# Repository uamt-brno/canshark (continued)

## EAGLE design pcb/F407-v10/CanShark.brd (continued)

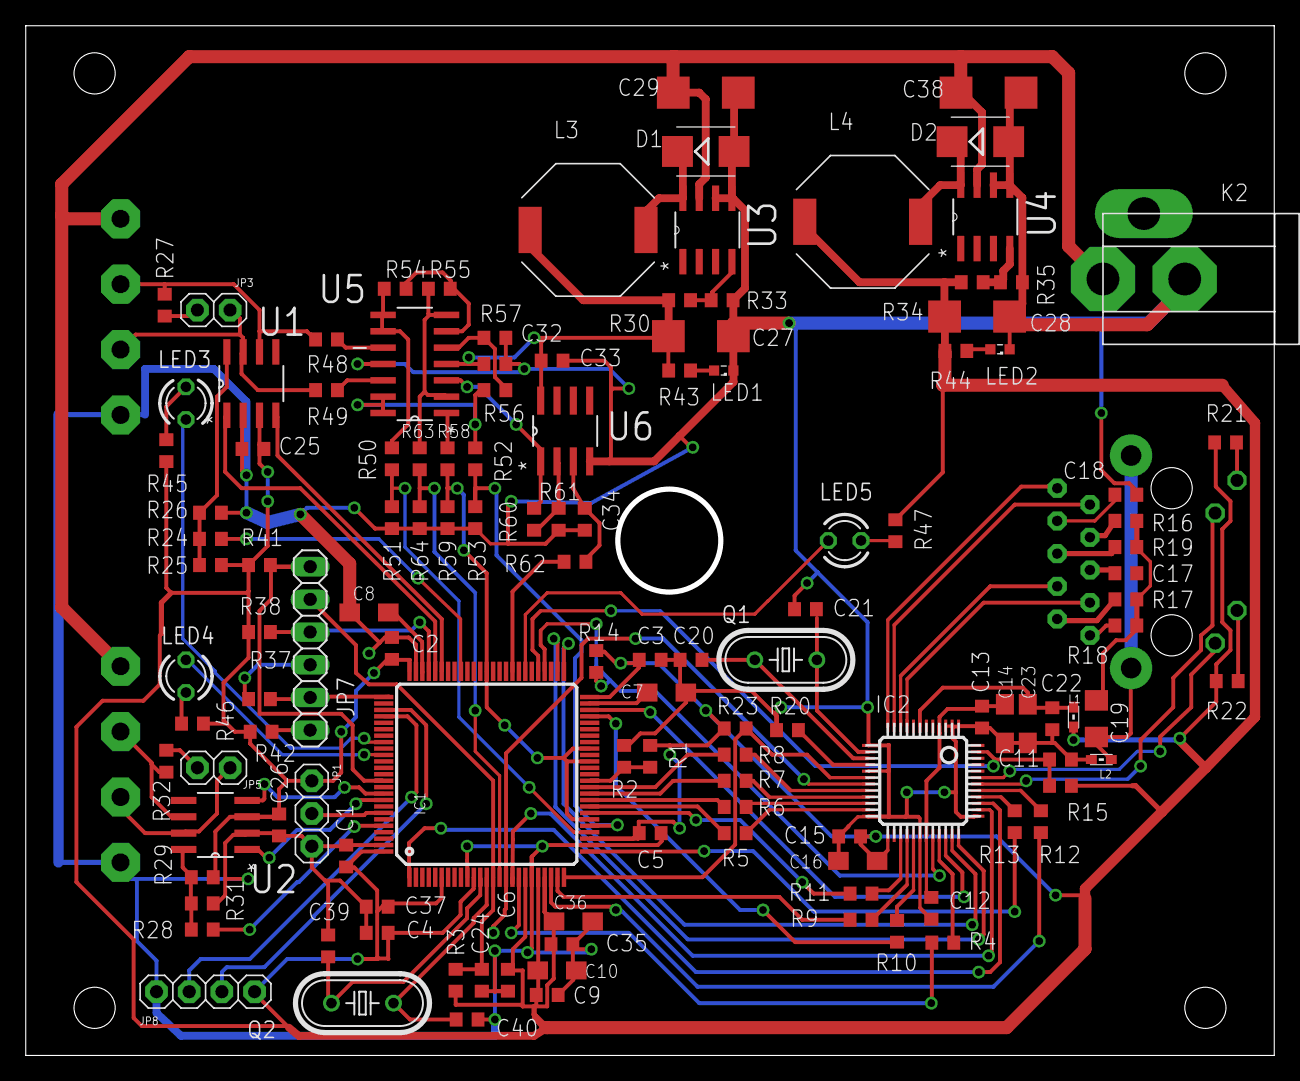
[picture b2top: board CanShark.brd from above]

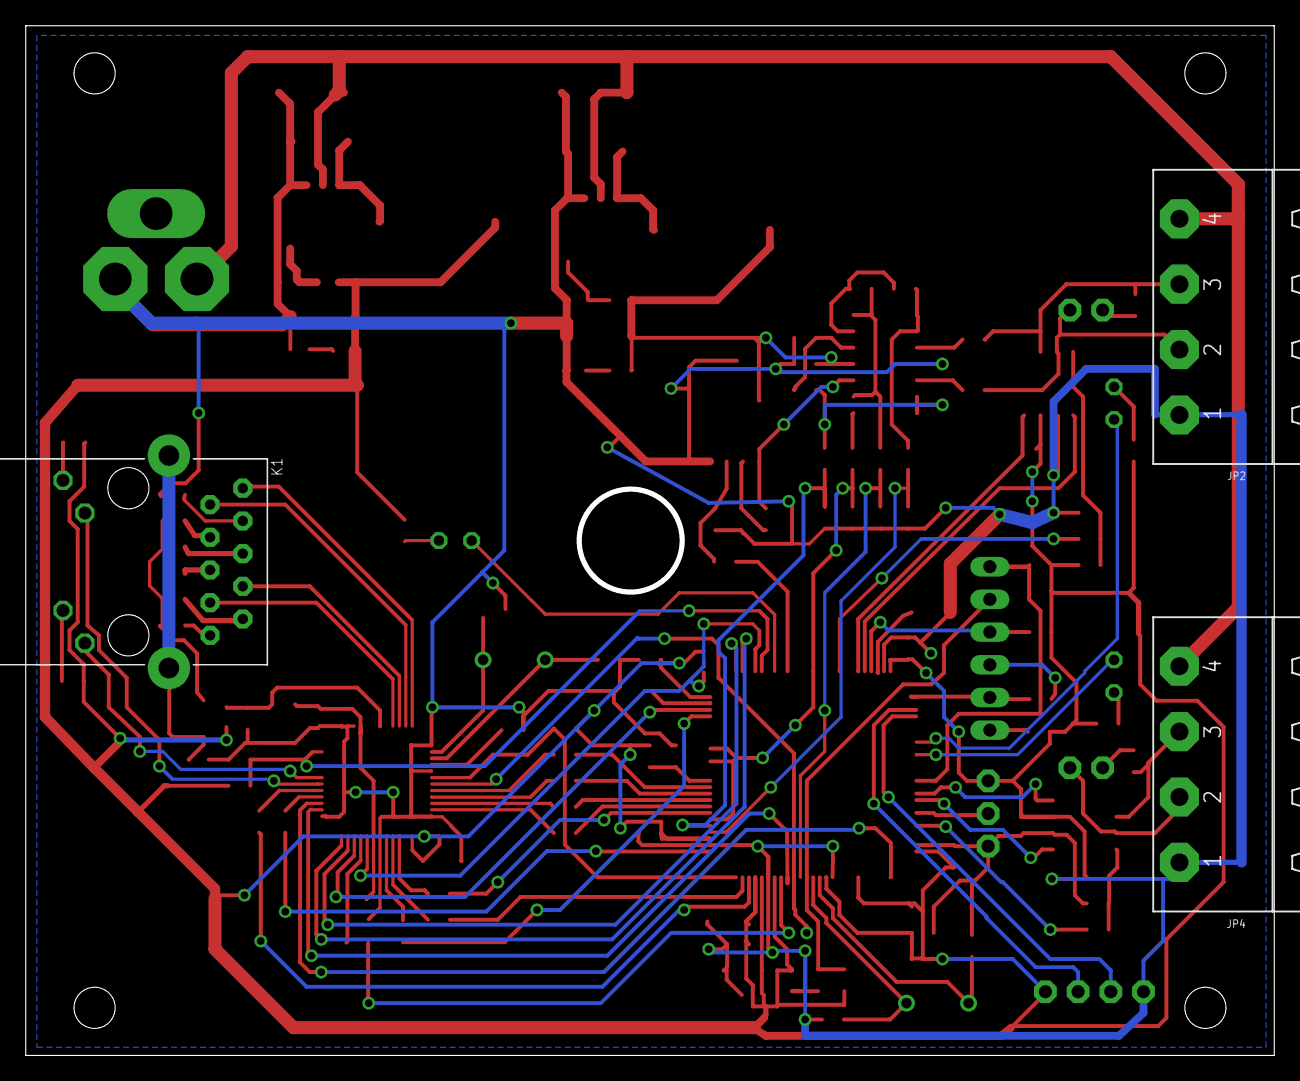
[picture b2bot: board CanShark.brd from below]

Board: 2 copper layers, 97.0 x 80.0 mm, 129 parts (3 on the bottom side), 109 nets.

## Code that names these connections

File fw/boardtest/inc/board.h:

#ifndef BOARD_H_INCLUDED
#define BOARD_H_INCLUDED

/* other pins:
 * SWDIO		PA13
 * SWCLK		PA14
 * BOOT1		PB2
 * SWO			PB3
 */


/******************************************************************************
 * LED configuration
 ******************************************************************************/

#define LED_PIN_CAN1	PD2				/* OH */
#define LED_PIN_CAN2	PD4				/* OH */
#define LED_PIN_GLOBAL	PD10				/* OH */

/******************************************************************************
 * Serial port configuration
 ******************************************************************************/

#define SER_PORT	USART3
#define SER_RCC		RCC_USART3
#define SER_AF		GPIO_AF7
#define SER_PIN_TX	PC10
#define SER_PIN_RX	PC11

/******************************************************************************
 * Ethernet MII port configuration
 ******************************************************************************/

#define MII_AF		GPIO_AF11
#define MII_PIN_MDC	PC1
#define MII_PIN_MDIO	PA2

#define MII_PIN_CRS	PA0
#define MII_PIN_COL	PA3

#define MII_PIN_RXC	PA1
#define MII_PIN_RXER	PB10
#define MII_PIN_RXDV	PA7
#define MII_PIN_RXD0	PC4
#define MII_PIN_RXD1	PC5
#define MII_PIN_RXD2	PB0
#define MII_PIN_RXD3	PB1

#define MII_PIN_TXC	PC3
#define MII_PIN_TXEN	PB11
#define MII_PIN_TXD0	PB12
#define MII_PIN_TXD1	PB13
#define MII_PIN_TXD2	PC2
#define MII_PIN_TXD3	PE2

#define MII_PIN_INTRP	PB15				/* I IRQ */
#define MII_PIN_RST	PD8				/* OH */

/******************************************************************************
 * Trigger pins configuration
 ******************************************************************************/

#define TR2_PIN_OE	PE8				/* OH */
#define TR2_PIN_D	PE9				/* OH */
#define TR2_PIN_I	PE10				/* I IRQ */
#define TR1_PIN_D	PE11				/* OH */
#define TR1_PIN_I	PE12				/* I IRQ */
#define TR1_PIN_OE	PE13				/* OH */

/******************************************************************************
 * CAN configuration
 ******************************************************************************/

#define PCAN1_AF	GPIO_AF9
#define PCAN2_AF	GPIO_AF9

#define PCAN1_PIN_RX	PA11
#define PCAN1_PIN_TX	PA12
#define PCAN2_PIN_RX	PB5
#define PCAN2_PIN_TX	PB6

#define PCAN1_PIN_MODE	PA8				/* O HiZ */
#define PCAN2_PIN_MODE	PB9				/* O HiZ */


#endif // BOARD_H_INCLUDED

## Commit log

2013-09-18 Directory structure
2013-09-18 Add canhark-console
2013-09-18 Add ignored files Ordered using
2013-09-18 [DISSECTOR] Rename the file to meet the board
2013-09-18 [FW] Added version working on F417 board
2013-09-18 [FW] Ignore generated files
2013-09-20 Add support for displaying Transmitted frames, corrected timing, utilized ethernet packet to have multiple frames in it (maximum of 256 bytes)
2013-09-20 [Dissector] Splitted out canopen dissector from main CAN message engine
2013-09-22 [canshark] Rewritten to have shared code for canshark and canshark-gui
2014-02-09 [Dissector] Speed-up the dissection of packet data using LUT
2014-02-09 [Dissector] Add CanOpen SDO dissection engine
2014-02-09 [Dissector] Properly manage the CAN dissector tree
2014-02-09 [Dissector] Optimize speed
2014-02-09 [sw/canshark-gui] Add packet statistics
2014-02-09 [canshark-gui] Add first version of GUI
2014-02-09 Correct the timestamp display.
2014-02-09 [canshark-gui] Add ignored folders
2014-02-09 Oprava zobrazeni cyklu CAN sbernice ikdyz nejsou zpravy
2014-02-09 Add cycle log for CAN2
2014-02-09 [sw/canshark-gui] Add the Canopen cycle log, first version
2014-02-09 Pridan vypocet delky zpravy (bez vsunutych bitu)
2014-02-09 [sw/canshark-console] Add argument parsing, rewritten to event driven packet capture.
2014-02-09 [sw/canshark-console] Add parameter configuration
2014-02-09 Switched to the new lib
2014-02-10 Updated to the new libopencm3
2014-02-11 Updated to the new libopencm3, beeter build process
2014-02-11 Build the lwip141 library independently on the main file.
2014-05-07 [pcb] Merged all modifications to pcb from Jakub Skalicky
    board manufactured version 1.0
2014-05-14 [pcb] change mounting hole position, increase the isolation gap
2014-05-22 [sw/canshark-gui] Add CanBusHistogram class
2014-05-22 [sw/canshark-gui] Add histogram component
2014-05-22 [sw/canshark-gui] Change main form for using histogram component
2014-06-02 [pcb] change texts of PCB
2014-06-02 Add EM::Blocks project
2014-06-02 [fw]Change pinout for CanShark board, add prescaler to main LED toggle
    (removed some unnecessary definitions. Cleaned code.)
2014-06-02 [sw/canshark-gui] Avoid resource memleak. Pens must be disposed
2014-06-05 [pcb] New PCB layout CanShark v2.0
    This layout has been based on Jakub Skalicky's V10 layout.
    The main differences are:
    * Size of the board truncated to be fabricated in ITEAD studio.
    * Power supply scheme changed, only power from application is enabled.
    * Removed analog measurement because it was currently not used in software
    * Added synchronization port (possible input or output with TTL 3.3V level to trig scope meter)
2014-07-02 [fw] Board testing firmware added. No tests currently valid
2014-07-02 [fw/canshark] remove dependency on work
2014-07-02 [fw/boardtest] cleaning
2014-07-02 [fw/boardtest] Style check for C++ and C,
2014-07-02 [fw/brdtest] Stylecheck compatible with C++
    Based on QEMU patch v4 03/10
    nable checkpatch.pl to apply the same checks as C source files for
    C++ files with .cpp extensions. It also adds some exceptions for C++
    sources to suppress errors for:
    - <> used in C++ template arguments (e.g. template <class T>)
    - :: used to represent namespaces (e.g. SomeClass::method())
2014-07-02 [fw/test] Initialize all GPIOs
2014-07-02 [fw/test] Board test preliminary work
2014-07-02 [fw/test] Make pinout definitions through board
2014-07-06 [fw/test] CAN link NAND tree test
2014-07-07 [fw/test] Declare PINS, use serial port for logging
2014-07-07 [fw/boardtest] Add CAN physical driver delay measurement
2014-07-14 [sw/gui] Add channel config property window
2014-07-14 [sw/gui] Fully implement the new analysis data flow.
2014-07-14 [sw/gui] Removing unnecessary code
2014-07-14 [sw/gui] Use Concurrent version of Dictionary instead of locking one
2014-07-14 [sw/gui] Implement fully splitted Model-view architecture. Model is now independent on View
2014-07-14 [sw/gui] Update the grid view to work with new Analysis feature
2014-07-14 [sw/gui] Completely remove DataReceived event handler
2014-07-14 [sw/gui] Resolution of StdID/ExtID is up to displayer.
2014-07-14 [sw/gui] Add SourceID parsing object
2014-07-14 [sw/gui] Grid with correct hex positions
2014-07-14 [sw/gui] Completely rewritten analyzers to use non-locking dictionaries
2014-07-14 [sw/gui] Populate objects to easily parse and print ObjectID's
2014-07-14 [sw/gui] Better simulation of Canopen cycle
2014-07-14 [sw/gui] Better formatting in Canopen cycle log
2014-07-14 [sw/gui] Complete rework of GUI. First look at messages
2014-07-14 [sw/gui] Optimization: stop waiting only if stopping or data arrived.
2014-07-14 [sw/gui] Refactoring boards to its own directorz and namespace
2014-07-14 [sw/gui] Raise receiving thread priority
2014-07-14 [sw/gui] Complete refactorization of the core. SLOW ! (10k packets analyzed per second - needs investigation!)
2014-07-14 [sw/gui] Optimize cycle log
2014-07-14 [sw/gui] More cleaning and optimization of Matrix
2014-07-14 [sw/gui] Optimization of grid display
2014-07-14 [sw/gui] Make PortStatistics analyzer more effecient.
2014-07-14 [sw/gui] Correct bus load compuation, optimization running on hardware
2014-07-14 [sw/gui] Optimization of CanopenCycleLog
2014-07-14 [sw/gui] Slight optimization
2014-07-14 [sw/gui] Display the full message log
2014-07-14 [sw/gui] some restructurialization
